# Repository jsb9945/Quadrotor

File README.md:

# Quadrotor

제어 PCB 제작(KiCAD) + Control 코드

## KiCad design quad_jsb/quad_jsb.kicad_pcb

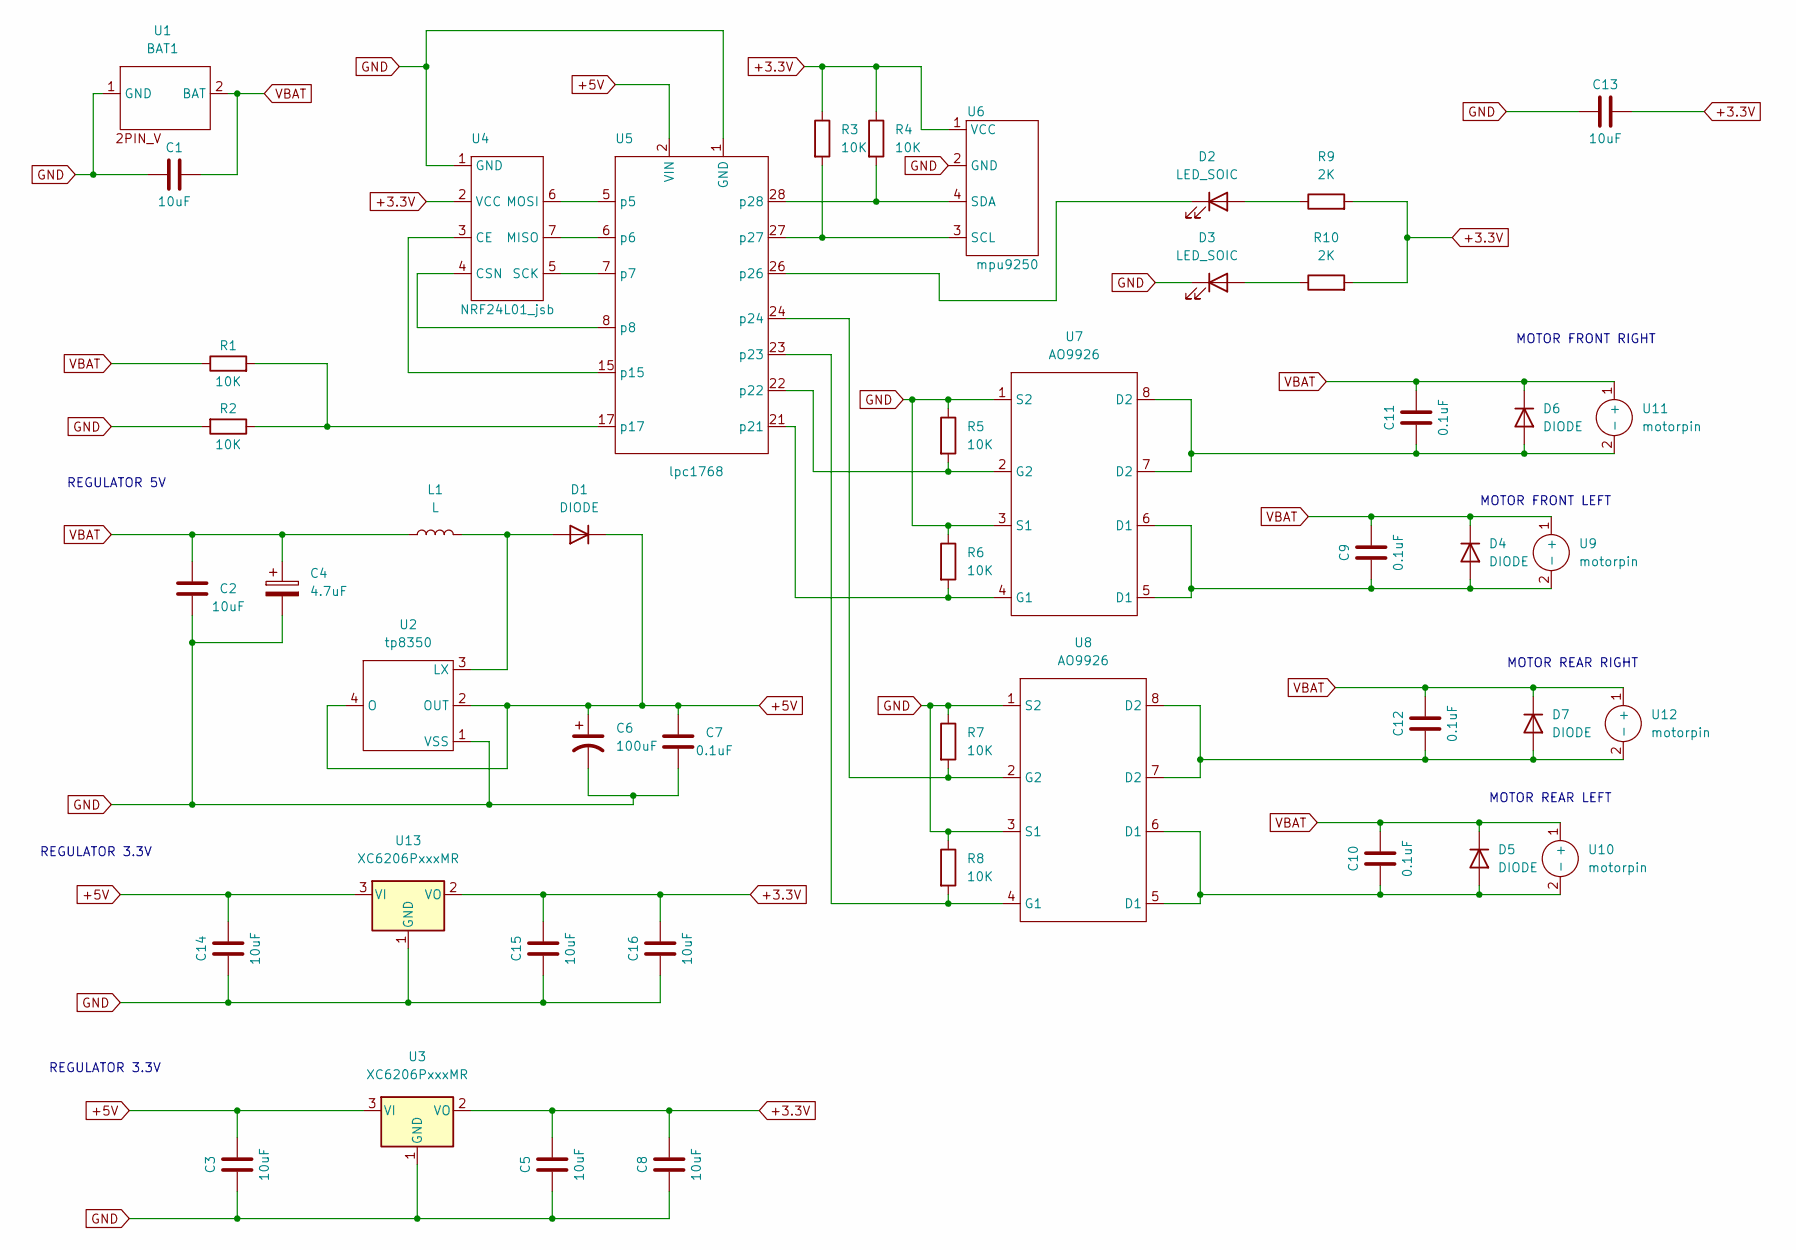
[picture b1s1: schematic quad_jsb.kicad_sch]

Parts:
C1, C2, C3, C5, C8, C13, C14, C15, C16: 10uF; C_0603_1608Metric_Pad1.08x0.95mm_HandSolder
C4: 4.7uF; C_0805_2012Metric_Pad1.18x1.45mm_HandSolder
C6: 100uF; CP_EIA-3528-21_Kemet-B_Pad1.50x2.35mm_HandSolder
C7, C9, C10, C11, C12: 0.1uF; C_0805_2012Metric_Pad1.18x1.45mm_HandSolder
D1: DIODE; D_T-1_P5.08mm_Horizontal
D2, D3: LED_SOIC; LED_0603_1608Metric_Pad1.05x0.95mm_HandSolder
D4, D5, D6, D7: DIODE; D_0603_1608Metric_Pad1.05x0.95mm_HandSolder
L1: L; L_TracoPower_TCK-047_5.2x5.8mm
R1, R2, R3, R4, R5, R6, R7, R8: 10K; R_0603_1608Metric_Pad0.98x0.95mm_HandSolder
R9, R10: 2K; R_0603_1608Metric_Pad0.98x0.95mm_HandSolder
U1: BAT1; BATHOLE
U2: tp8350; SOT-89-3_Handsoldering
U3, U13: XC6206PxxxMR; SOT-23
U4: NRF24L01_jsb; NRF24L01
U5: lpc1768; LPC1768
U6: mpu9250; PinSocket_1x10_P2.54mm_Vertical
U7, U8: AO9926; SOIC-8_3.9x4.9mm_P1.27mm
U9, U10, U11, U12: motorpin; motor_pin

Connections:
+3.3V: C5.2, C8.2, C13.2, C15.2, C16.2, R3.1, R4.1, R9.2, R10.2, U3.2 (VO), U4.2 (VCC), U6.1 (VCC), U13.2 (VO)
+5V: C3.2, C6.1, C7.2, C14.2, D1.2 (K), U2.2 (OUT), U2.4 (O), U3.3 (VI), U5.2 (VIN), U13.3 (VI)
GND: C1.1, C2.1, C3.1, C4.2, C5.1, C6.2, C7.1, C8.1, C13.1, C14.1, C15.1, C16.1, D3.1 (K), R2.2, R5.1, R6.1, R7.1, R8.1, U1.1 (GND), U2.1 (VSS), U3.1 (GND), U4.1 (GND), U5.1 (GND), U6.2 (GND), U7.1 (S2), U7.3 (S1), U8.1 (S2), U8.3 (S1), U13.1 (GND)
unnamed: C9.1, D4.1 (A), U7.5 (D1), U7.6 (D1), U9.2 (-)
unnamed: C10.1, D5.1 (A), U8.5 (D1), U8.6 (D1), U10.2 (-)
unnamed: C11.1, D6.1 (A), U7.7 (D2), U7.8 (D2), U11.2 (-)
unnamed: C12.1, D7.1 (A), U8.7 (D2), U8.8 (D2), U12.2 (-)
unnamed: D1.1 (A), L1.2, U2.3 (LX)
unnamed: D2.1 (K), U5.26 (p26)
unnamed: D2.2 (A), R9.1
unnamed: D3.2 (A), R10.1
unnamed: R1.2, R2.1, U5.17 (p17)
unnamed: R3.2, U5.27 (p27), U6.3 (SCL)
unnamed: R4.2, U5.28 (p28), U6.4 (SDA)
unnamed: R5.2, U5.22 (p22), U7.2 (G2)
unnamed: R6.2, U5.21 (p21), U7.4 (G1)
unnamed: R7.2, U5.24 (p24), U8.2 (G2)
unnamed: R8.2, U5.23 (p23), U8.4 (G1)
unnamed: U4.3 (CE), U5.15 (p15)
unnamed: U4.4 (CSN), U5.8 (p8)
unnamed: U4.5 (SCK), U5.7 (p7)
unnamed: U4.6 (MOSI), U5.5 (p5)
unnamed: U4.7 (MISO), U5.6 (p6)
VBAT: C1.2, C2.2, C4.1, C9.2, C10.2, C11.2, C12.2, D4.2 (K), D5.2 (K), D6.2 (K), D7.2 (K), L1.1, R1.1, U1.2 (BAT), U9.1 (+), U10.1 (+), U11.1 (+), U12.1 (+)

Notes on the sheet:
REGULATOR 3.3V
MOTOR FRONT LEFT
MOTOR REAR RIGHT
REGULATOR 5V
MOTOR REAR LEFT
MOTOR FRONT RIGHT

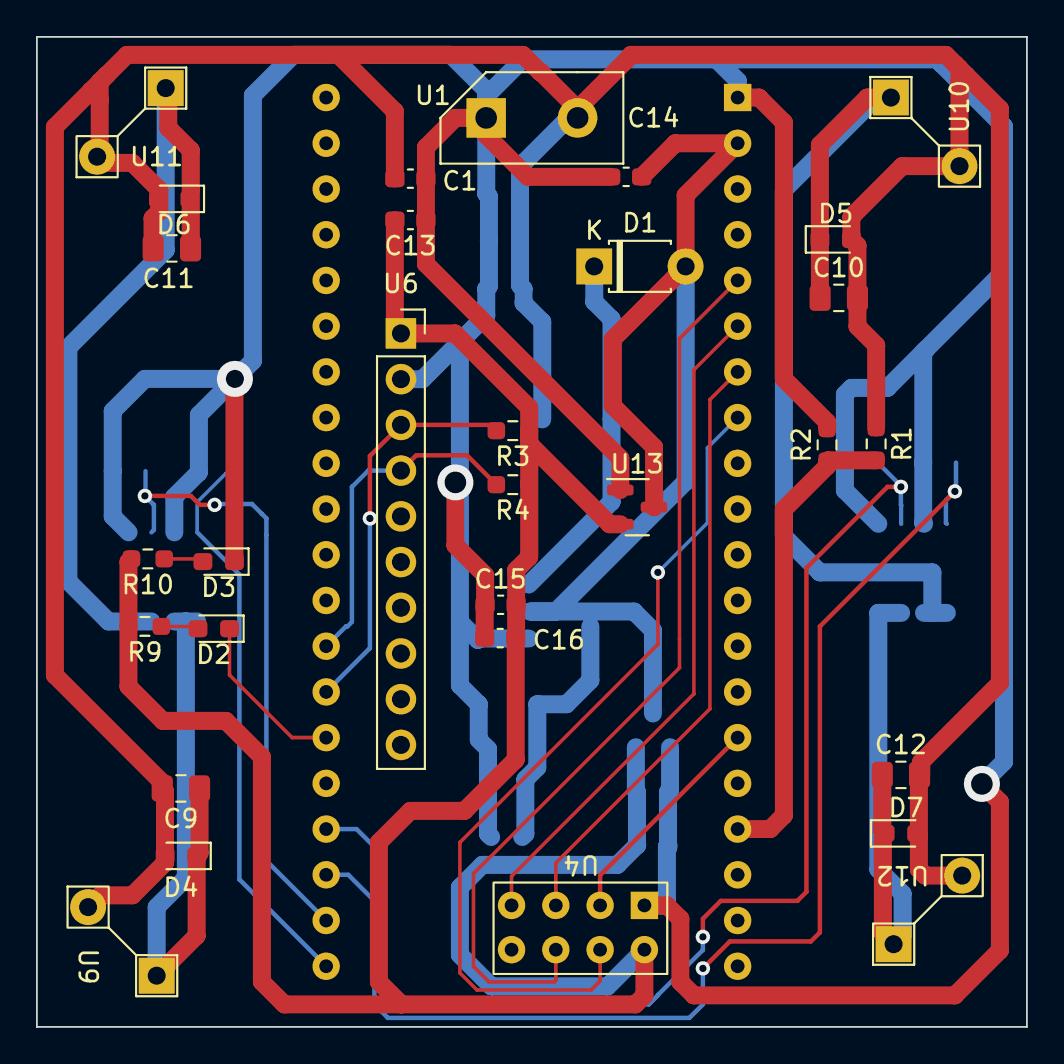
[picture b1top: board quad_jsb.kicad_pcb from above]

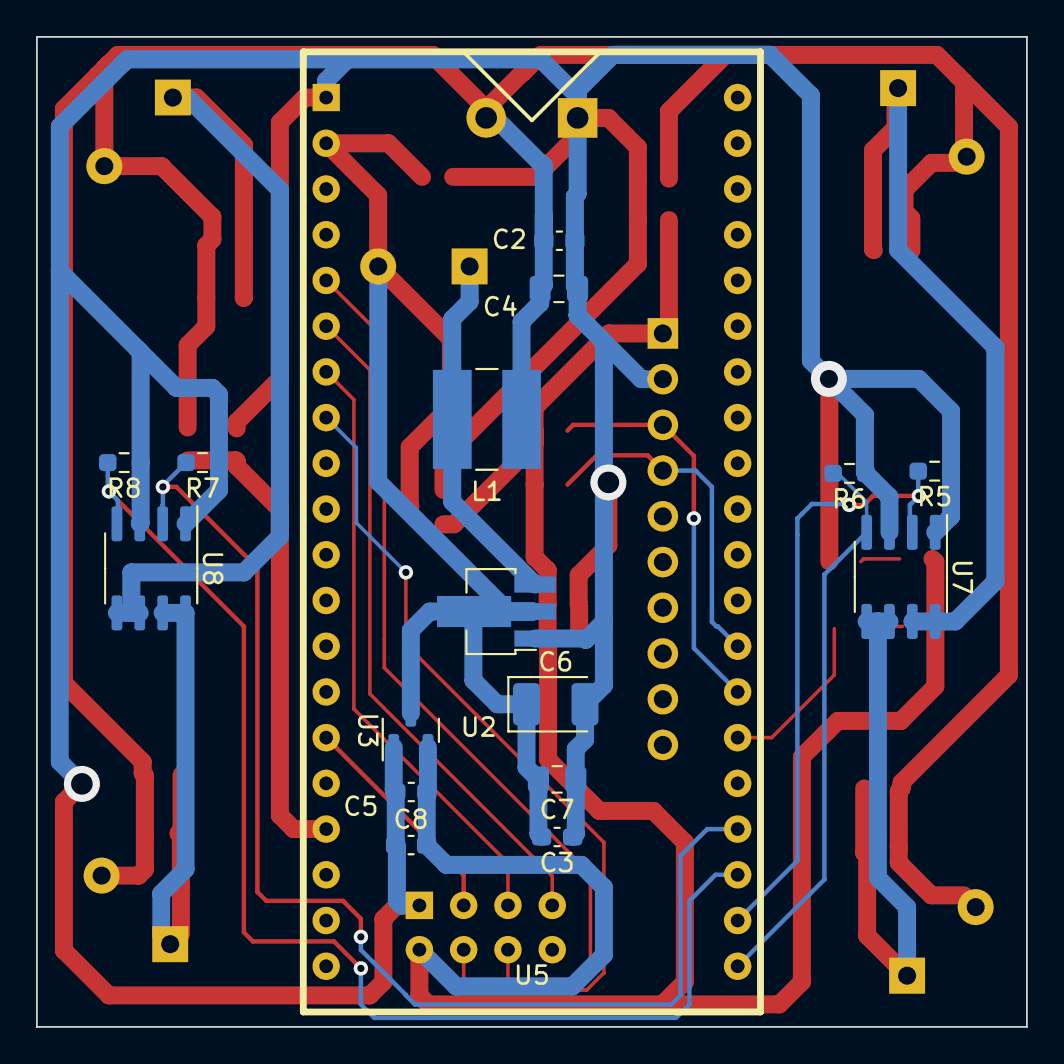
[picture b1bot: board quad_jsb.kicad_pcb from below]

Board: 2 copper layers, 55.0 x 55.0 mm, 47 parts (17 on the bottom side), 24 nets.
